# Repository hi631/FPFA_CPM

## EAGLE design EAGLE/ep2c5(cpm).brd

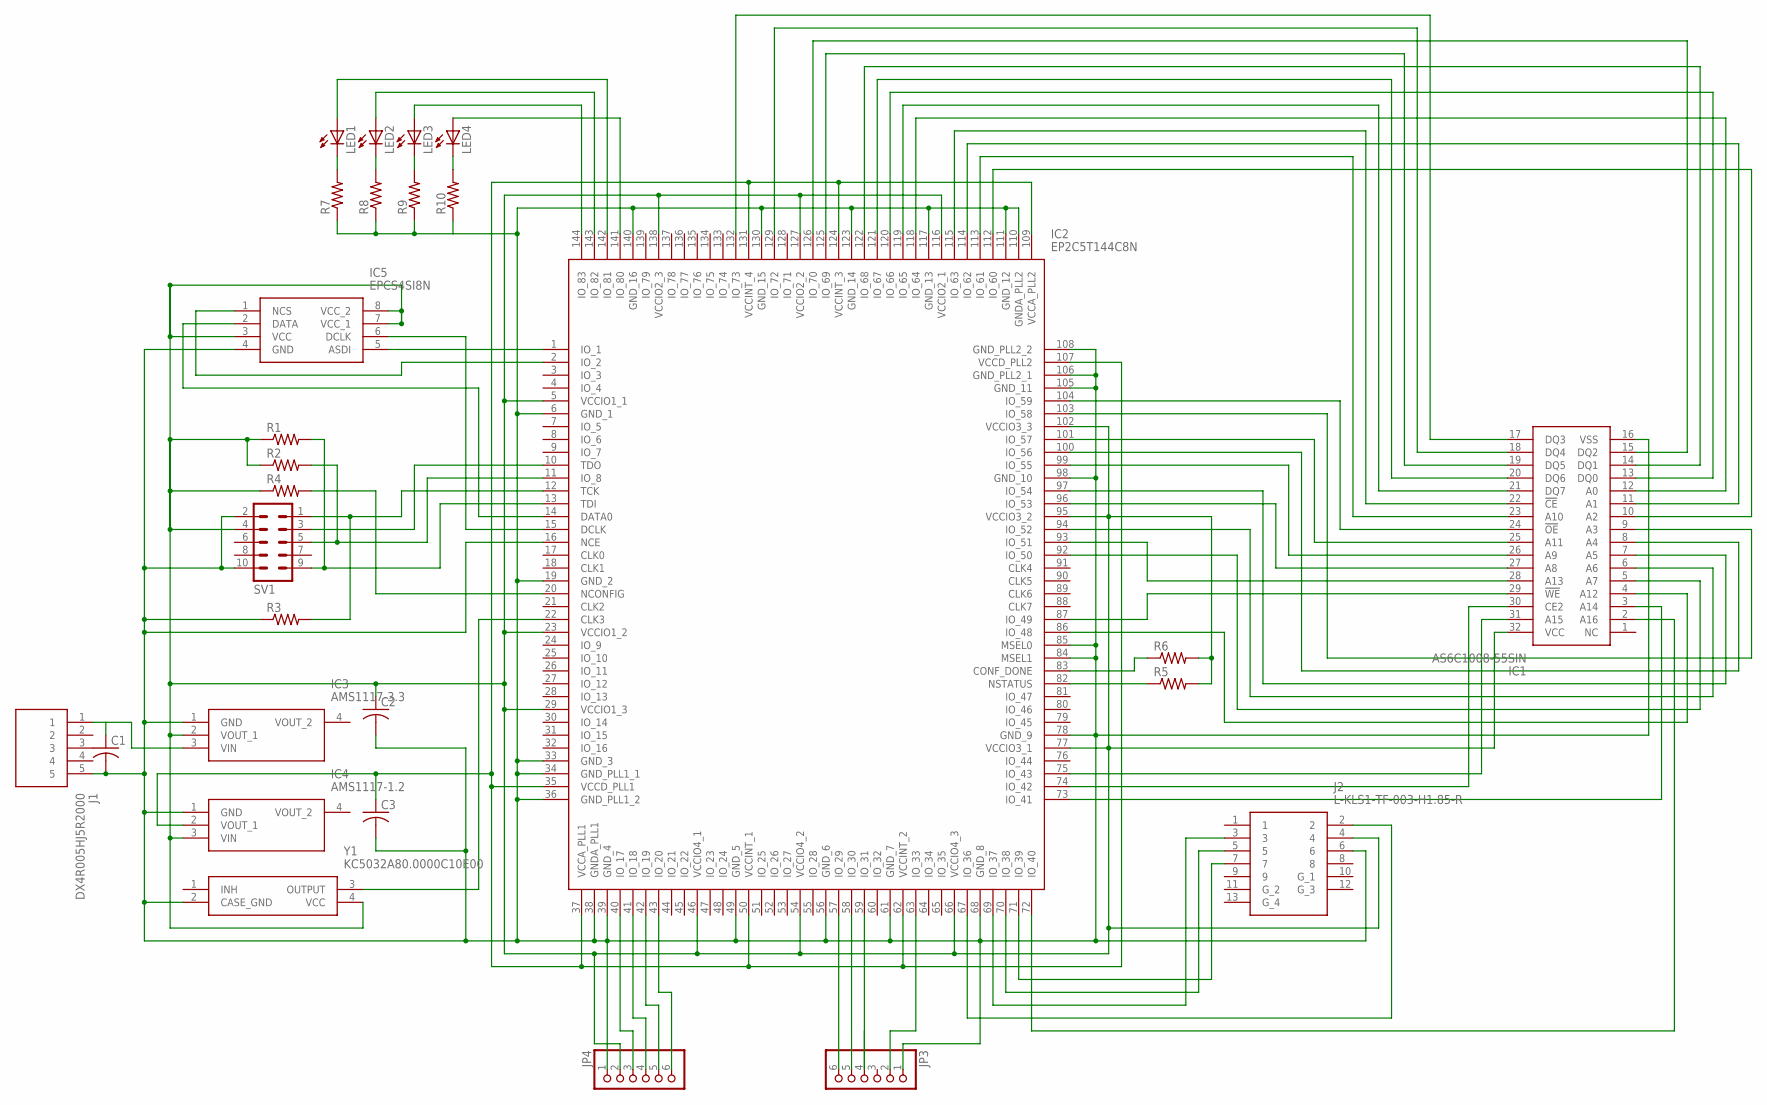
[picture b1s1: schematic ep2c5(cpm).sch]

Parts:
C1, C2, C3: C-USC0805; C0805
IC1: AS6C1008-55SIN; SOIC127P1407X299-32N
IC2: EP2C5T144C8N; QFP50P2200X2200X160-144N
IC3: AMS1117-3.3; SOT229P700X180-4N
IC4: AMS1117-1.2; SOT229P700X180-4N
IC5: EPCS4SI8N; SOIC127P600X175-8N
J1: DX4R005HJ5R2000; DX4R005HJ5
J2: L-KLS1-TF-003-H1.85-R
JP3, JP4: PINHD-1X6; 1X06
LED1, LED2, LED3, LED4: LEDCHIP-LED0805; CHIP-LED0805
R1, R2, R3, R4, R5, R6, R7, R8, R9, R10: R-US_R0805; R0805
SV1: MA05-2
Y1: KC5032A80.0000C10E00; KC5032A12.0000CM0E00

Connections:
GND: C1.2, C2.2, C3.2, IC1.16 (VSS), IC2.6 (GND_1), IC2.16 (NCE), IC2.19 (GND_2), IC2.33 (GND_3), IC2.34 (GND_PLL1_1), IC2.36 (GND_PLL1_2), IC2.38 (GNDA_PLL1), IC2.39 (GND_4), IC2.49 (GND_5), IC2.56 (GND_6), IC2.61 (GND_7), IC2.68 (GND_8), IC2.78 (GND_9), IC2.84 (MSEL1), IC2.85 (MSEL0), IC2.98 (GND_10), IC2.105 (GND_11), IC2.106 (GND_PLL2_1), IC2.108 (GND_PLL2_2), IC2.110 (GNDA_PLL2), IC2.111 (GND_12), IC2.117 (GND_13), IC2.123 (GND_14), IC2.130 (GND_15), IC2.140 (GND_16), IC3.1 (GND), IC4.1 (GND), IC5.4 (GND), J1.5, J2.6, JP3.1, JP4.1, R3.1, R7.1, R8.1, R9.1, R10.1, SV1.2, SV1.10, Y1.2 (CASE_GND)
unnamed: C3.1, IC2.35 (VCCD_PLL1), IC2.37 (VCCA_PLL1), IC2.50 (VCCINT_1), IC2.62 (VCCINT_2), IC2.107 (VCCD_PLL2), IC2.109 (VCCA_PLL2), IC2.124 (VCCINT_3), IC2.131 (VCCINT_4), IC4.2 (VOUT_1)
unnamed: IC2.1 (IO_1), IC5.5 (ASDI)
unnamed: IC2.2 (IO_2), IC5.1 (NCS)
unnamed: IC2.15 (DCLK), IC5.6 (DCLK)
unnamed: IC2.14 (DATA0), IC5.2 (DATA)
unnamed: IC2.12 (TCK), R3.2, SV1.1
unnamed: IC2.10 (TDO), SV1.3
unnamed: IC2.13 (TDI), R1.2, SV1.9
unnamed: IC2.11 (IO_8), R2.2, SV1.5
unnamed: IC1.31 (A15), IC2.75 (IO_43)
unnamed: IC2.20 (NCONFIG), R4.2
unnamed: IC2.82 (NSTATUS), R5.1
unnamed: IC2.83 (CONF_DONE), R6.1
unnamed: IC2.22 (CLK3), Y1.3 (OUTPUT)
unnamed: IC1.30 (CE2), IC2.74 (IO_42)
unnamed: IC1.3 (A14), IC2.73 (IO_41)
unnamed: IC1.2 (A16), IC2.72 (IO_40)
unnamed: IC1.4 (A12), IC2.86 (IO_48)
unnamed: IC1.29 (!WE), IC2.87 (IO_49)
unnamed: IC1.5 (A7), IC2.92 (IO_50)
unnamed: IC1.28 (A13), IC2.93 (IO_51)
unnamed: IC1.6 (A6), IC2.94 (IO_52)
unnamed: IC1.27 (A8), IC2.96 (IO_53)
unnamed: IC1.7 (A5), IC2.97 (IO_54)
unnamed: IC1.26 (A9), IC2.99 (IO_55)
unnamed: IC1.8 (A4), IC2.100 (IO_56)
unnamed: IC1.25 (A11), IC2.101 (IO_57)
unnamed: IC1.9 (A3), IC2.103 (IO_58)
unnamed: IC1.24 (!OE), IC2.104 (IO_59)
unnamed: IC1.10 (A2), IC2.112 (IO_60)
unnamed: IC1.23 (A10), IC2.113 (IO_61)
unnamed: IC1.11 (A1), IC2.114 (IO_62)
unnamed: IC1.22 (!CE), IC2.115 (IO_63)
unnamed: IC1.12 (A0), IC2.118 (IO_64)
unnamed: IC1.21 (DQ7), IC2.119 (IO_65)
unnamed: IC1.13 (DQ0), IC2.120 (IO_66)
unnamed: IC1.20 (DQ6), IC2.121 (IO_67)
unnamed: IC1.14 (DQ1), IC2.122 (IO_68)
unnamed: IC1.15 (DQ2), IC2.126 (IO_70)
unnamed: IC1.19 (DQ5), IC2.125 (IO_69)
unnamed: IC1.18 (DQ4), IC2.129 (IO_72)
unnamed: IC1.17 (DQ3), IC2.132 (IO_73)
unnamed: IC2.71 (IO_39), J2.7
unnamed: IC2.70 (IO_38), J2.5
unnamed: IC2.69 (IO_37), J2.3
unnamed: IC2.67 (IO_36), J2.2
unnamed: IC2.58 (IO_30), JP3.5
unnamed: IC2.57 (IO_29), JP3.6
unnamed: IC2.63 (IO_33), JP3.2
unnamed: IC2.59 (IO_31), JP3.4
unnamed: IC2.40 (IO_17), JP4.3
unnamed: IC2.41 (IO_18), JP4.4
unnamed: IC2.42 (IO_19), JP4.5
unnamed: IC2.43 (IO_20), JP4.6
unnamed: LED1.C, R7.2
unnamed: LED2.C, R8.2
unnamed: LED3.C, R9.2
unnamed: IC2.144 (IO_83), LED3.A
unnamed: IC2.143 (IO_82), LED2.A
unnamed: IC2.142 (IO_81), LED1.A
unnamed: LED4.C, R10.2
unnamed: IC2.141 (IO_80), LED4.A
V3.3: C2.1, IC1.32 (VCC), IC2.5 (VCCIO1_1), IC2.23 (VCCIO1_2), IC2.29 (VCCIO1_3), IC2.46 (VCCIO4_1), IC2.54 (VCCIO4_2), IC2.66 (VCCIO4_3), IC2.77 (VCCIO3_1), IC2.95 (VCCIO3_2), IC2.102 (VCCIO3_3), IC2.116 (VCCIO2_1), IC2.127 (VCCIO2_2), IC2.138 (VCCIO2_3), IC3.2 (VOUT_1), IC4.3 (VIN), IC5.3 (VCC), IC5.7 (VCC_1), IC5.8 (VCC_2), J2.4, JP4.2, R1.1, R2.1, R4.1, R5.2, R6.2, SV1.4, Y1.4 (VCC)
V5.0: C1.1, IC3.3 (VIN), J1.1

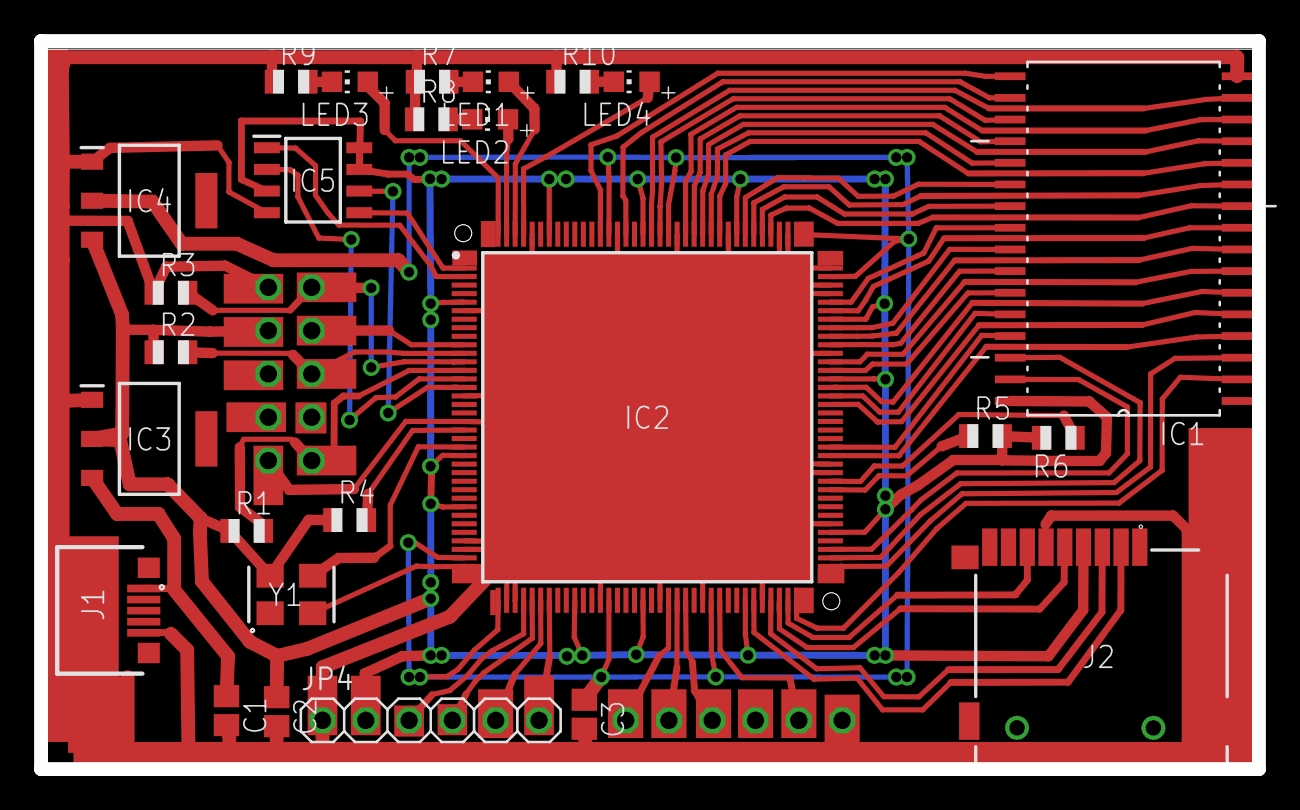
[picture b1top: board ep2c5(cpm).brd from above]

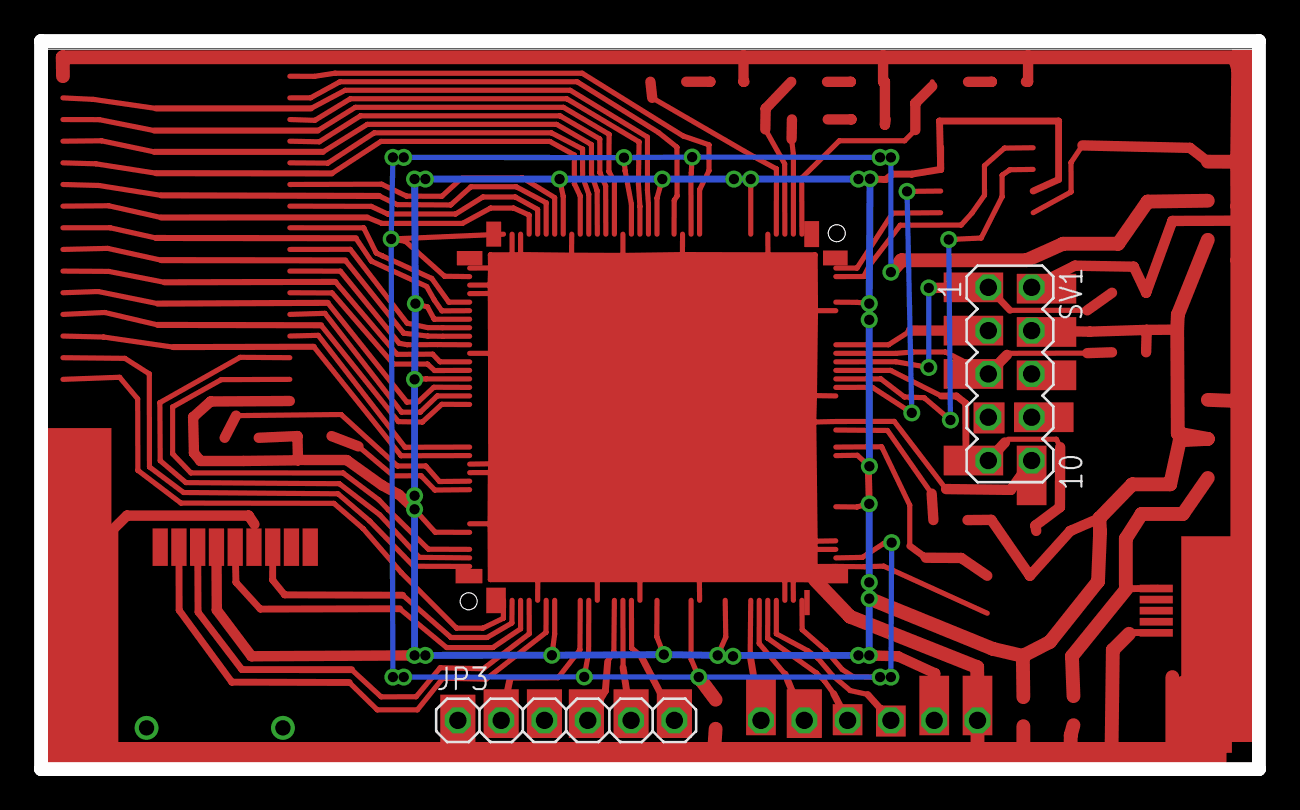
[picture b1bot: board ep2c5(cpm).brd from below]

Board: 2 copper layers, 71.4 x 42.7 mm, 28 parts (2 on the bottom side), 65 nets.

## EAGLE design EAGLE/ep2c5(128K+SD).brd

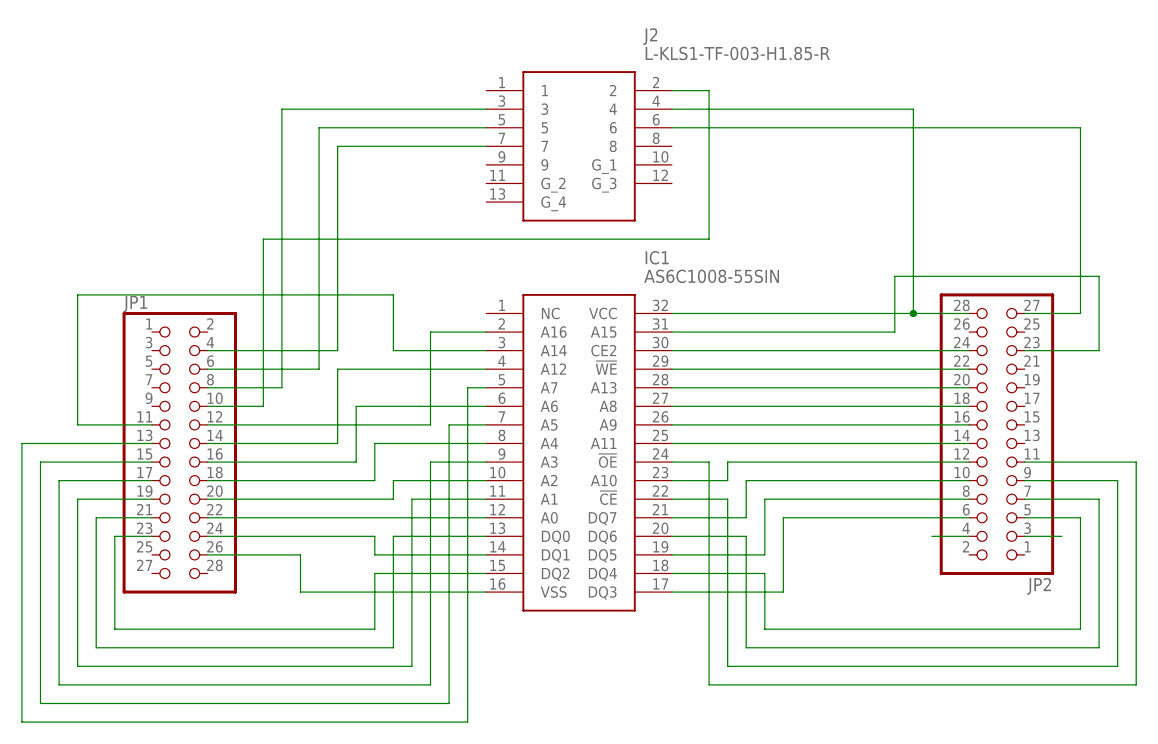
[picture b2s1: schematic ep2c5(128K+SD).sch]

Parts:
IC1: AS6C1008-55SIN; SOIC127P1407X299-32N
J2: L-KLS1-TF-003-H1.85-R
JP1, JP2: PINHD-2X14; 2X14

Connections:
unnamed: J2.6, JP2.27
unnamed: IC1.15 (DQ2), JP1.23
unnamed: J2.2, JP1.10
unnamed: IC1.14 (DQ1), JP1.24
unnamed: IC1.12 (A0), JP1.22
unnamed: IC1.10 (A2), JP1.20
unnamed: IC1.8 (A4), JP1.18
unnamed: IC1.6 (A6), JP1.16
unnamed: J2.3, JP1.8
unnamed: J2.5, JP1.6
unnamed: J2.7, JP1.4
unnamed: IC1.16 (VSS), JP1.26
unnamed: IC1.31 (A15), JP2.23
unnamed: IC1.4 (A12), JP1.14
unnamed: IC1.2 (A16), JP1.12
unnamed: IC1.13 (DQ0), JP1.21
unnamed: IC1.11 (A1), JP1.19
unnamed: IC1.9 (A3), JP1.17
unnamed: IC1.7 (A5), JP1.15
unnamed: IC1.5 (A7), JP1.13
unnamed: IC1.3 (A14), JP1.11
unnamed: IC1.17 (DQ3), JP2.6
unnamed: IC1.19 (DQ5), JP2.8
unnamed: IC1.21 (DQ7), JP2.10
unnamed: IC1.23 (A10), JP2.12
unnamed: IC1.18 (DQ4), JP2.5
unnamed: IC1.20 (DQ6), JP2.7
unnamed: IC1.22 (!CE), JP2.9
unnamed: IC1.24 (!OE), JP2.11
unnamed: IC1.25 (A11), JP2.14
unnamed: IC1.26 (A9), JP2.16
unnamed: IC1.27 (A8), JP2.18
unnamed: IC1.32 (VCC), J2.4, JP2.28
unnamed: IC1.28 (A13), JP2.20
unnamed: IC1.29 (!WE), JP2.22
unnamed: IC1.30 (CE2), JP2.24

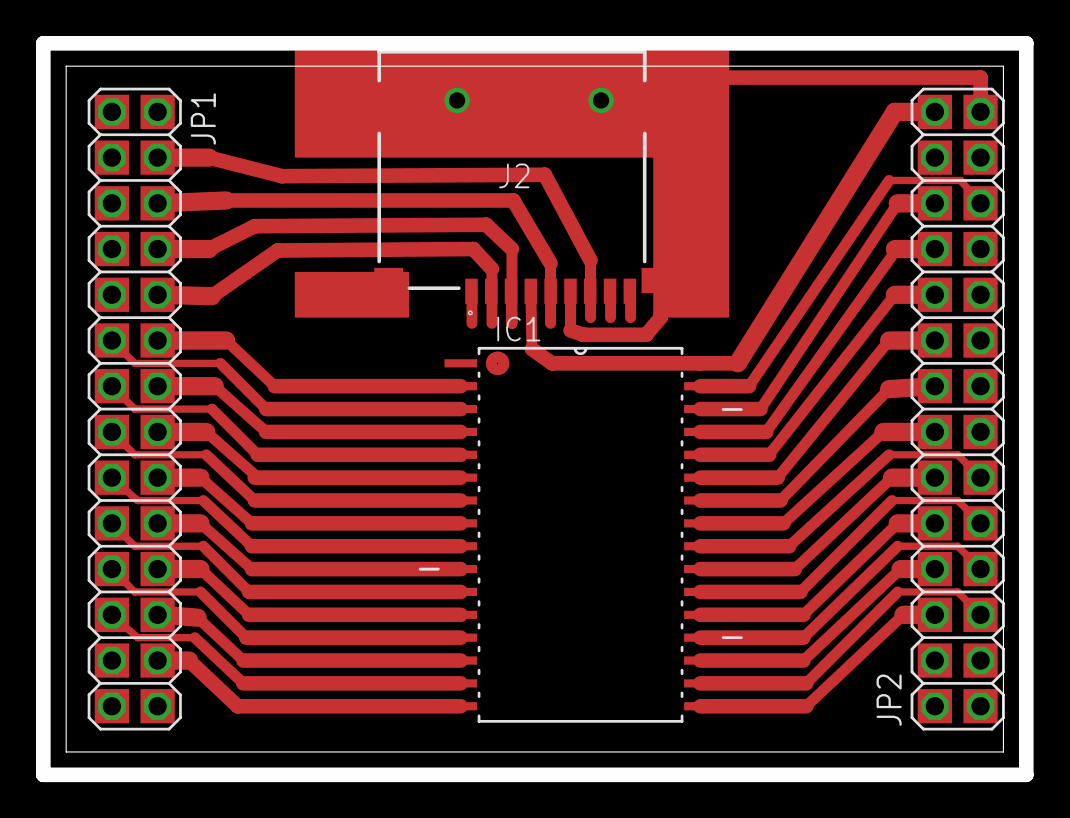
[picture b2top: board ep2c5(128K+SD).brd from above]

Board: 2 copper layers, 54.6 x 40.6 mm, 4 parts (0 on the bottom side), 36 nets.

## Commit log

2020-03-13 new Signed-off-by: hi631 <hi631@ac.auone-net.jp>
